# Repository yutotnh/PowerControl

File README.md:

# PowerControl

## 機能の説明
本基板は、電源の制御回路です。

最大3つのスイッチを用いて電源のON/OFF制御ができます。

常時許容電流は70A程度です(銅箔厚:1ozの場合。使用する環境やMOSFETの性能によって低下します)。

各スイッチはAND構成で接続しているため、全てのスイッチがONになったときのみ電流が流れます。

## 使い方

### スイッチの構成

本基板には3つのスイッチを接続するコネクタが用意されています。

スイッチの構成は以下です。

| リファレンス | 基板上の表記 | 対象スイッチ      | ON               | 対応ソルダジャンパ |
| ------------ | ------------ | ----------------- | ---------------- | ------------------ |
| J1           | IC Input     | マイコン等の入力  | フォトカプラがON | JP1                |
| J2           | EMS SW2      | 非常停止スイッチ2 | スイッチがON     | JP2                |
| J3           | EMS SW1      | 非常停止スイッチ1 | スイッチがON     | JP3                |

動作チェック時など、一部のスイッチを接続しない場合は、接続しないスイッチの真下のソルダジャンパ(JP1~JP3)をショートすることで接続を省略することができます。

### スイッチの接続

#### IC Input

信号を絶縁するため、フォトカプラを通して電源を制御します。

Signal側のピンにマイコンの5Vや3.3V等の出力を入力、GND側にマイコンが使用しているGNDを入力してください。

#### EMS SW

非常停止スイッチ接続用のため、極性などは気にする必要はありません。

## 確認用LED

入力側と出力側の両方のON/OFF確認用LEDを用意しています。

LEDが点灯している場合ONの状態です。

LEDを実装する場合は、入力側と出力側で異なる色のLEDにすると状態を視認しやすくなると思います。

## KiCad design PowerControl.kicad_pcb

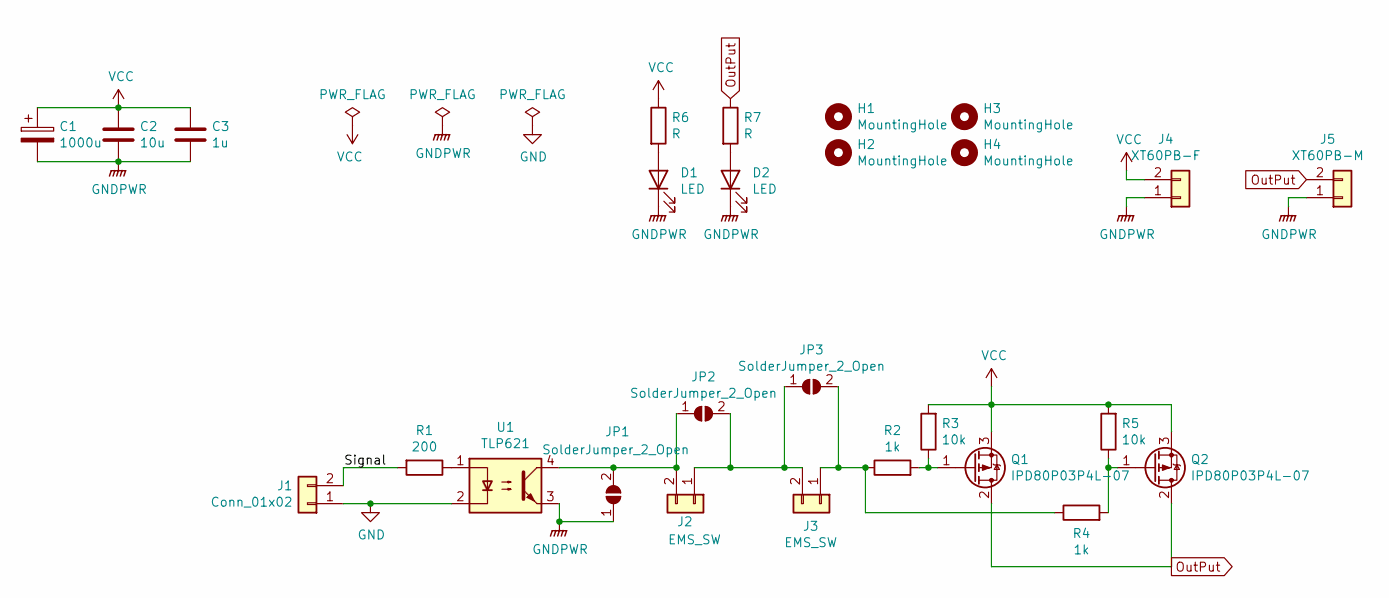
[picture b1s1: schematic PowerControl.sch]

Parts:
C1: 1000u; CP_Radial_D12.5mm_P5.00mm
C2: 10u; C_0805_2012Metric_Pad1.15x1.40mm_HandSolder
C3: 1u; C_0805_2012Metric_Pad1.15x1.40mm_HandSolder
D1, D2: LED; LED_0603_1608Metric_Pad1.05x0.95mm_HandSolder
H1, H2, H3, H4: MountingHole; MountingHole_3.2mm_M3
J1: Conn_01x02; PinHeader_1x02_P2.54mm_Vertical
J2, J3: EMS_SW; PinHeader_1x02_P2.54mm_Vertical
J4: XT60PB-F; AMASS_XT60-F_1x02_P7.20mm_Vertical
J5: XT60PB-M; AMASS_XT60-M_1x02_P7.20mm_Vertical
JP1, JP2, JP3: SolderJumper_2_Open; SolderJumper-2_P1.3mm_Open_TrianglePad1.0x1.5mm
Q1, Q2: IPD80P03P4L-07; TO-252-2
R1: 200; R_0603_1608Metric_Pad1.05x0.95mm_HandSolder
R2, R4: 1k; R_0603_1608Metric_Pad1.05x0.95mm_HandSolder
R3, R5: 10k; R_0603_1608Metric_Pad1.05x0.95mm_HandSolder
R6, R7: R; R_0603_1608Metric_Pad0.98x0.95mm_HandSolder
U1: TLP621; DIP-4_W7.62mm

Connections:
/Signal: J1.2, R1.2
GND: J1.1, U1.2
GNDPWR: C1.2, C2.2, C3.2, D1.1 (K), D2.1 (K), J4.1, J5.1, JP1.1 (A), U1.3
unnamed: D1.2 (A), R6.2
unnamed: D2.2 (A), R7.2
unnamed: J2.1, J3.2, JP2.2 (B), JP3.1 (A)
unnamed: J2.2, JP1.2 (B), JP2.1 (A), U1.4
unnamed: J3.1, JP3.2 (B), R2.1, R4.1
unnamed: Q1.1 (G), R2.2, R3.1
unnamed: Q2.1 (G), R4.2, R5.1
unnamed: R1.1, U1.1
OutPut: J5.2, Q1.2 (D), Q2.2 (D), R7.1
VCC: C1.1, C2.1, C3.1, J4.2, Q1.3 (S), Q2.3 (S), R3.2, R5.2, R6.1

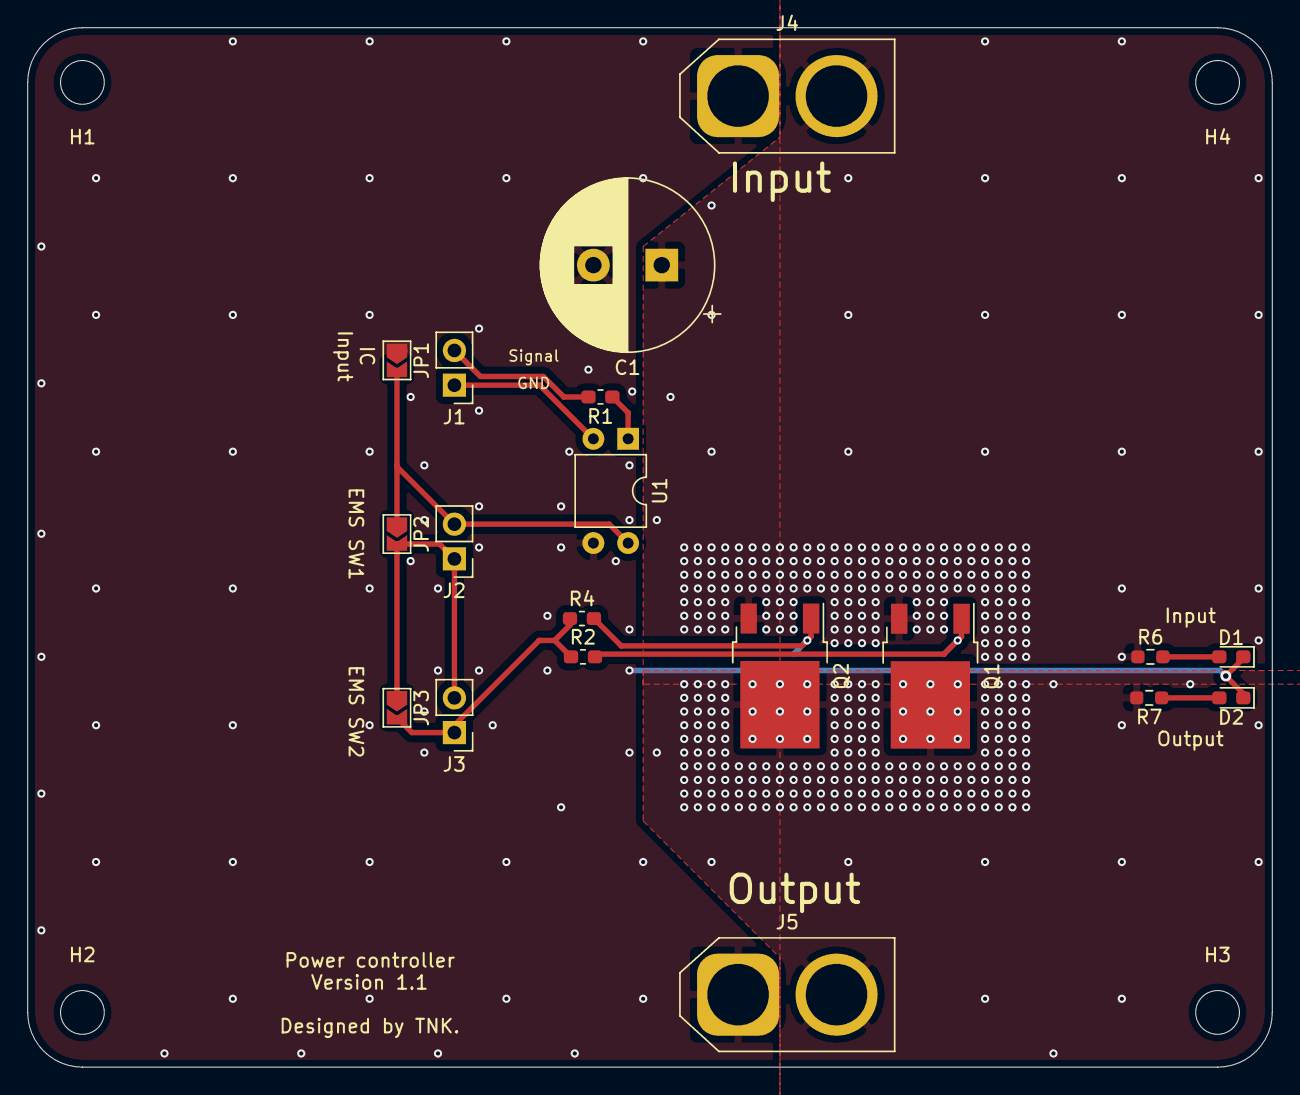
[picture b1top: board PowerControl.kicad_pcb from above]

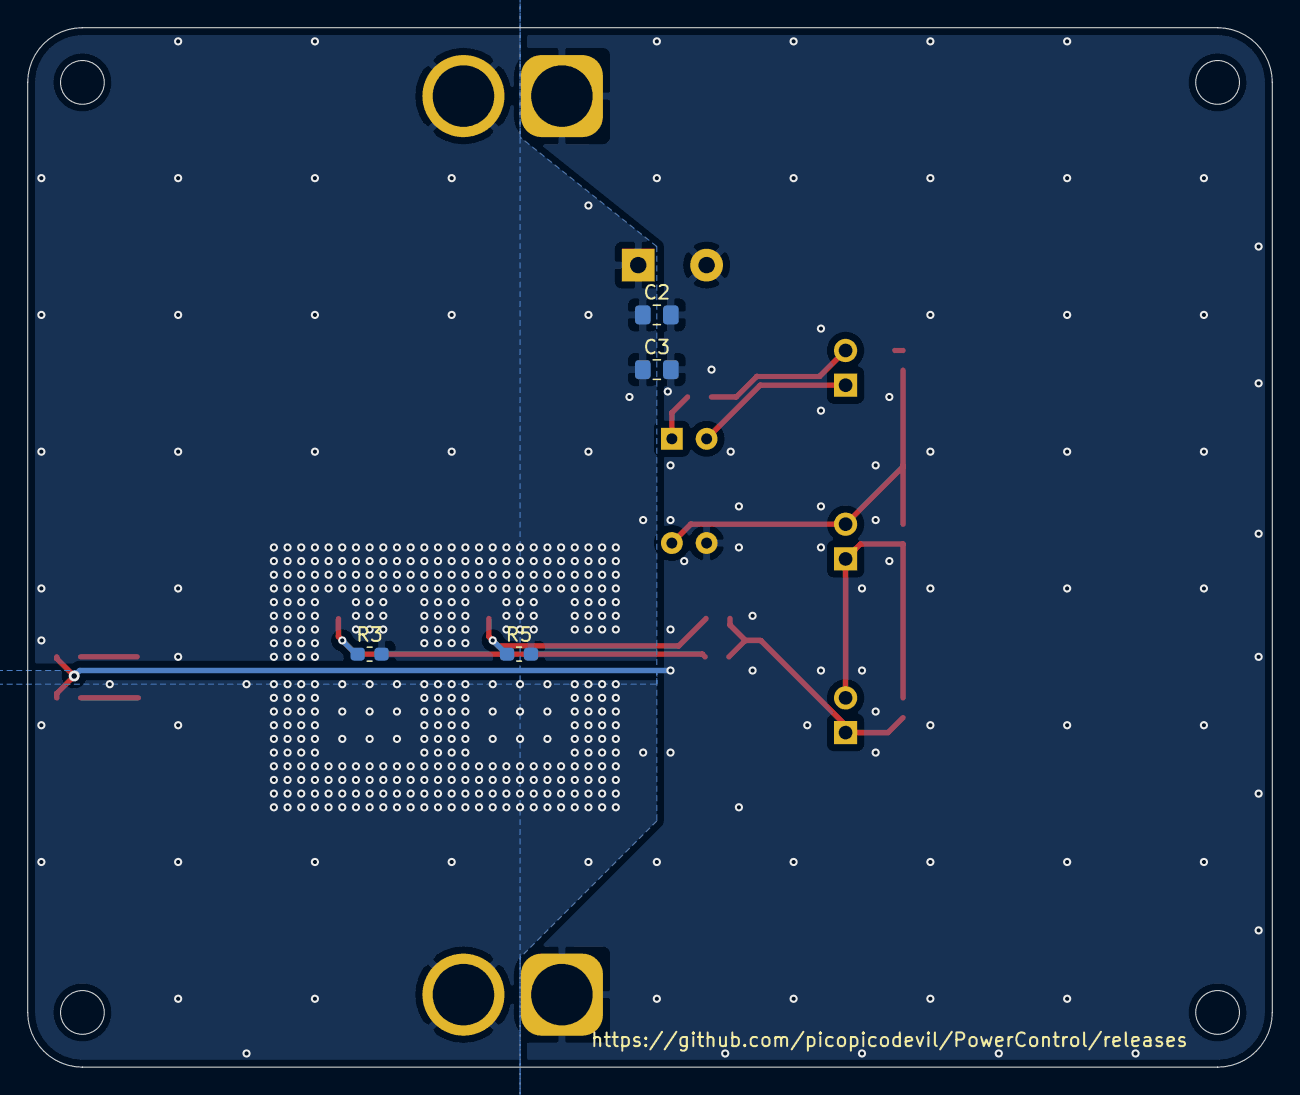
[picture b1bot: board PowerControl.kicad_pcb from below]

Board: 2 copper layers, 91.0 x 76.0 mm, 27 parts (4 on the bottom side), 13 nets.

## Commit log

2020-06-22 start project
    プロジェクトおよびファイルを作成
2020-06-23 change
    Eeschemaでの主な設計
2020-07-04 Add board
    基本的な設計が終了
2020-07-04 change Pch MOSFET name
    Pch MOSFETの名称をIPD80P03P4L-07に変更
2021-09-16 Update: .gitignoreにバックアップファイルを追加
2021-09-16 Remove: 不必要なファイルの削除
2021-09-16 Add: .dcm
2021-09-16 Update: 配線幅などの変更
2021-09-16 Fix: Pch MOSFETのゲートの印加電圧を修正(12V→GND)
2021-09-16 Update: ソルダージャンパの配置を変更
2021-09-16 Update: kicad_pcbに修正を変更
2021-09-16 Update: 配線の変更
2021-09-16 Update: シルクの修正
2021-09-16 Update: 導通確認用のLEDを配置
2021-09-16 Add README.md & image file
2021-09-18 Update: 常時許容電流の補足文を追加
2021-09-18 Update: 塗りつぶしの再実行
2021-09-21 Update: ガーバーファイルを出力
2021-09-24 Create LICENSE
